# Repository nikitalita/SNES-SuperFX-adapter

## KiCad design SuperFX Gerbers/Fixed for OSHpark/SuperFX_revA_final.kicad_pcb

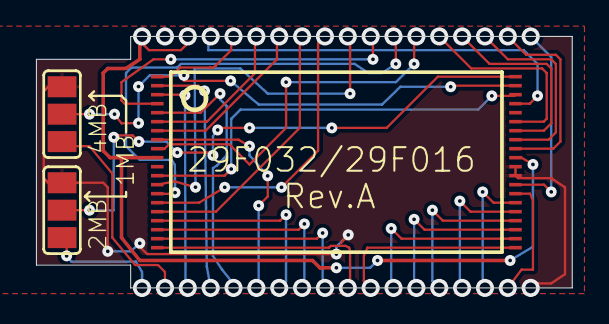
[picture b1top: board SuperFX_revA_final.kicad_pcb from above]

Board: 2 copper layers, 29.8 x 14.0 mm, 3 parts (0 on the bottom side), 4 nets.

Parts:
U$1: AM29F032B-E; 40-TSOP
UNK20, UNK21: SJ_2

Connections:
GND: U$1.29, U$1.30, UNK20.3, UNK21.3
unnamed: U$1.39, UNK21.2
unnamed: U$1.40, UNK20.2
VCC: U$1.10, U$1.12, U$1.31, U$1.38

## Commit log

2023-02-08 WIP changes
